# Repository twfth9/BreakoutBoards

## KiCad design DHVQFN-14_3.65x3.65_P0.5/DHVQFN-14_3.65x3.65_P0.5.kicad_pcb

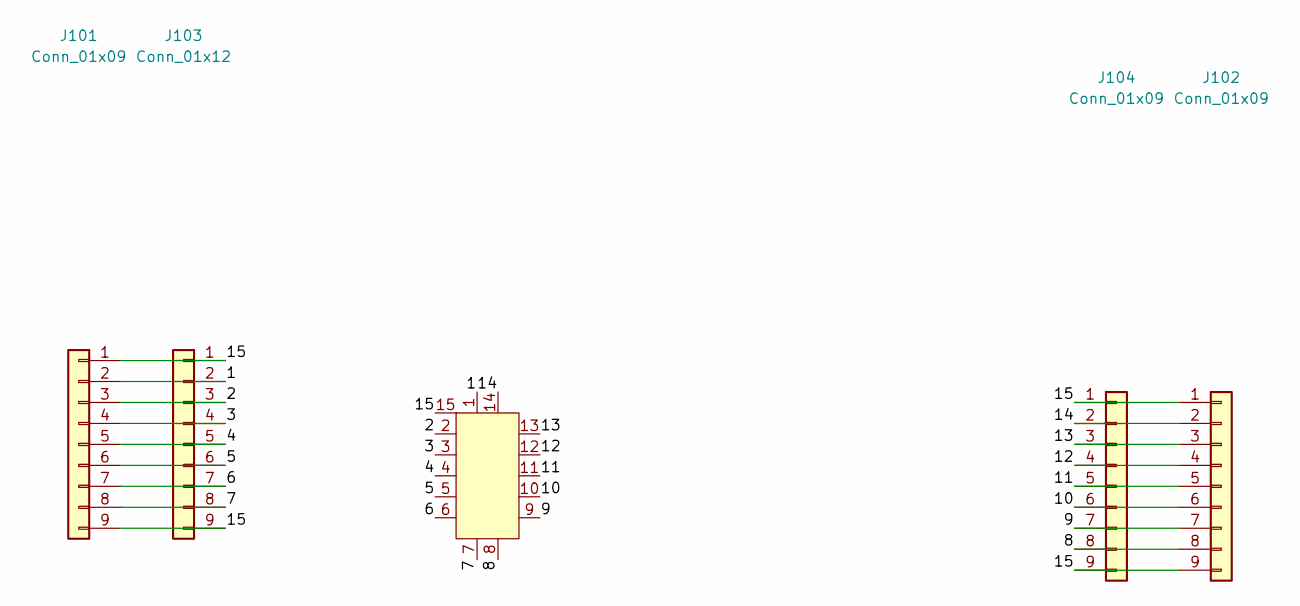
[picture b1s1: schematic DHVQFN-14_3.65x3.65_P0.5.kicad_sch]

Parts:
J101: Conn_01x09; PinHeader_1x09_P2.54mm_Vertical_SMD_Pin1Left
J102: Conn_01x09; PinHeader_1x09_P2.54mm_Vertical
J103: Conn_01x12; PinHeader_1x09_P2.54mm_Vertical
J104: Conn_01x09; PinHeader_1x09_P2.54mm_Vertical_SMD_Pin1Right
U101: DHVQFN-14; RGY14_2P05X2P05

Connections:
/1: J101.2, J103.2, U101.1
/2: J101.3, J103.3, U101.2
/3: J101.4, J103.4, U101.3
/4: J101.5, J103.5, U101.4
/5: J101.6, J103.6, U101.5
/6: J101.7, J103.7, U101.6
/7: J101.8, J103.8, U101.7
/8: J102.8, J104.8, U101.8
/9: J102.7, J104.7, U101.9
/10: J102.6, J104.6, U101.10
/11: J102.5, J104.5, U101.11
/12: J102.4, J104.4, U101.12
/13: J102.3, J104.3, U101.13
/14: J102.2, J104.2, U101.14
/15: J101.1, J101.9, J102.1, J102.9, J103.1, J103.9, J104.1, J104.9, U101.15

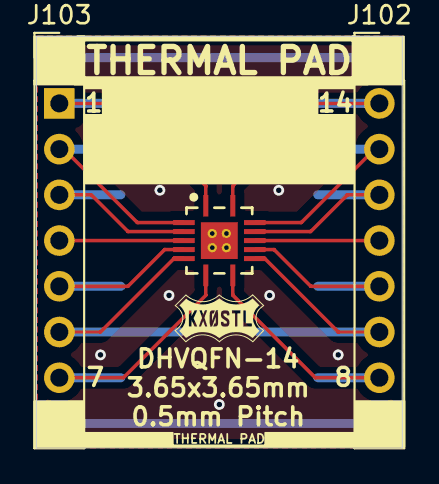
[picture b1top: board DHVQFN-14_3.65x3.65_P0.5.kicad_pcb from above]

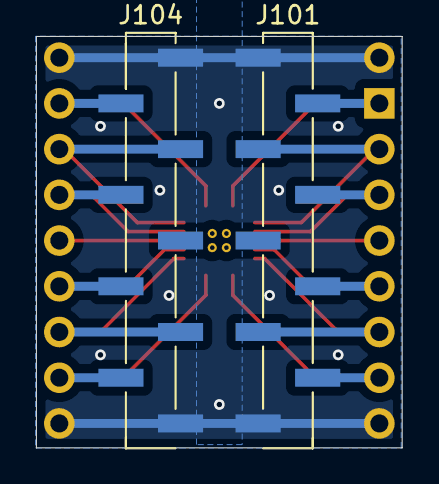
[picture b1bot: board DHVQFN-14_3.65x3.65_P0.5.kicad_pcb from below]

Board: 2 copper layers, 20.3 x 22.9 mm, 5 parts (2 on the bottom side), 15 nets.

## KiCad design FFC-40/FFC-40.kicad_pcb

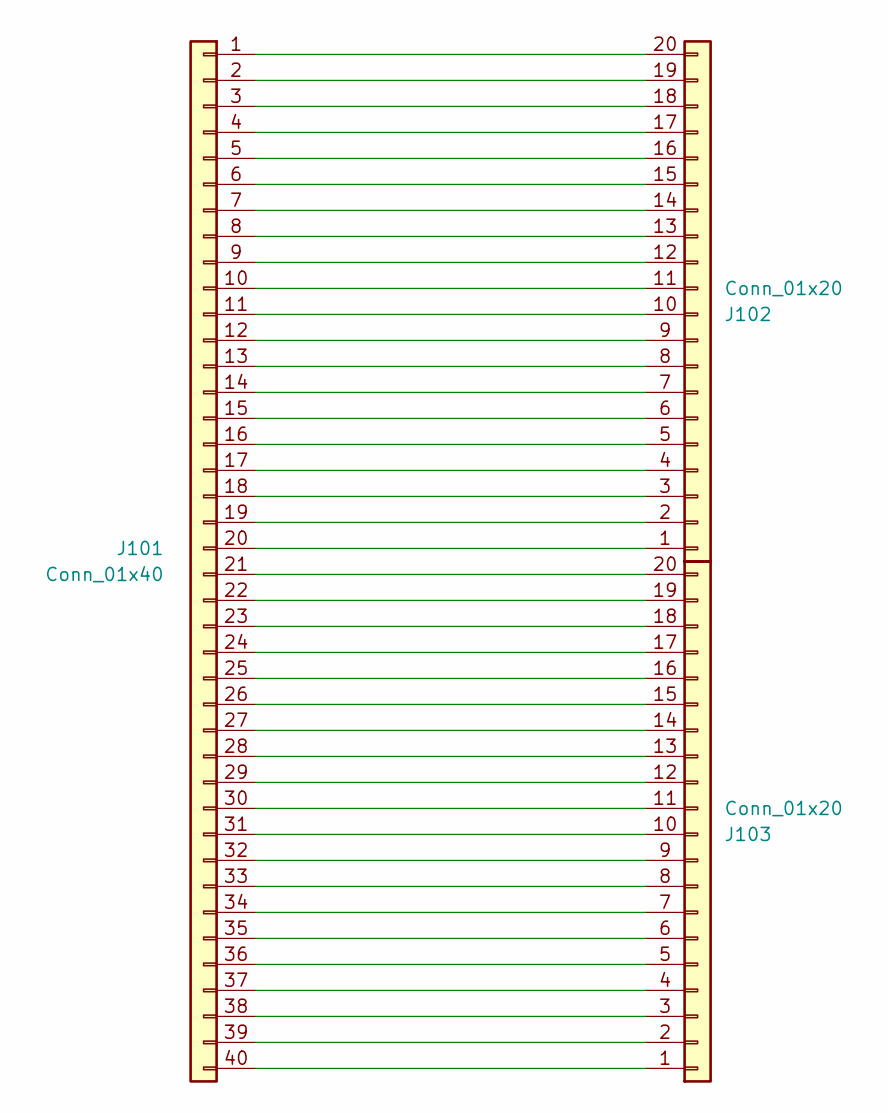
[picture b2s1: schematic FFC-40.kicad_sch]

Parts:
J101: Conn_01x40; Amphenol_F32R-1A7x1-11040_1x40-1MP_P0.5mm_Horizontal
J102, J103: Conn_01x20; PinHeader_1x20_P2.54mm_Vertical

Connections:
unnamed: J101.1, J102.20
unnamed: J101.2, J102.19
unnamed: J101.3, J102.18
unnamed: J101.4, J102.17
unnamed: J101.5, J102.16
unnamed: J101.6, J102.15
unnamed: J101.7, J102.14
unnamed: J101.8, J102.13
unnamed: J101.9, J102.12
unnamed: J101.10, J102.11
unnamed: J101.11, J102.10
unnamed: J101.12, J102.9
unnamed: J101.13, J102.8
unnamed: J101.14, J102.7
unnamed: J101.15, J102.6
unnamed: J101.16, J102.5
unnamed: J101.17, J102.4
unnamed: J101.18, J102.3
unnamed: J101.19, J102.2
unnamed: J101.20, J102.1
unnamed: J101.21, J103.20
unnamed: J101.22, J103.19
unnamed: J101.23, J103.18
unnamed: J101.24, J103.17
unnamed: J101.25, J103.16
unnamed: J101.26, J103.15
unnamed: J101.27, J103.14
unnamed: J101.28, J103.13
unnamed: J101.29, J103.12
unnamed: J101.30, J103.11
unnamed: J101.31, J103.10
unnamed: J101.32, J103.9
unnamed: J101.33, J103.8
unnamed: J101.34, J103.7
unnamed: J101.35, J103.6
unnamed: J101.36, J103.5
unnamed: J101.37, J103.4
unnamed: J101.38, J103.3
unnamed: J101.39, J103.2
unnamed: J101.40, J103.1

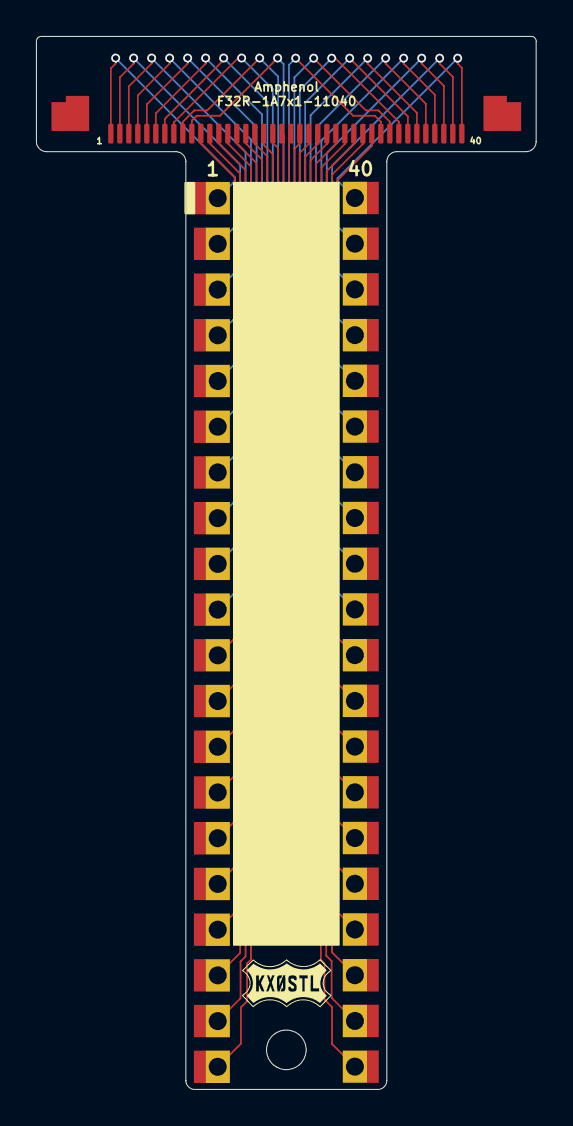
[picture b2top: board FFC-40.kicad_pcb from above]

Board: 2 copper layers, 27.8 x 58.5 mm, 3 parts (0 on the bottom side), 40 nets.

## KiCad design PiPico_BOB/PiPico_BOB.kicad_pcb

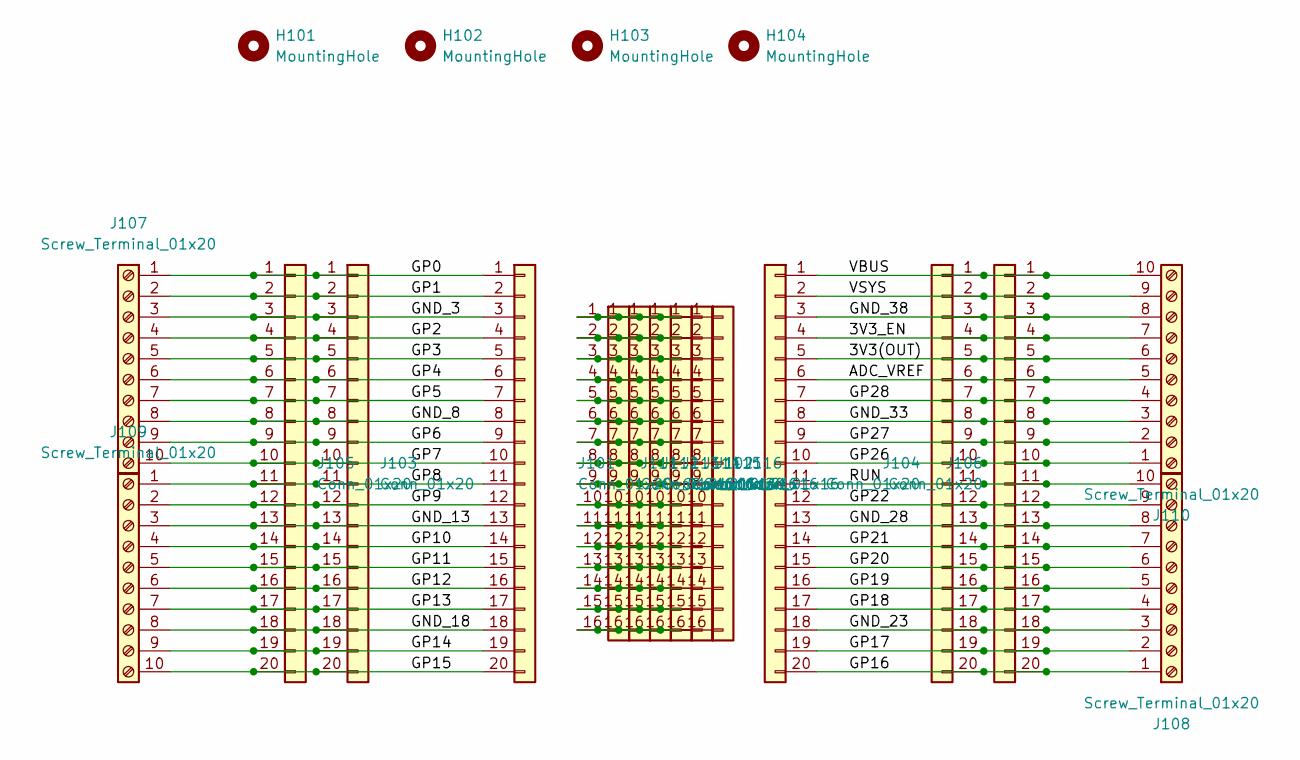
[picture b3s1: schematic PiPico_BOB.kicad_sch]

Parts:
H101, H102, H103, H104: MountingHole; MountingHole_2.2mm_M2
J101, J102, J103, J104: Conn_01x20; PinSocket_1x20_P2.54mm_Vertical
J105, J106: Conn_01x20; PinHeader_1x20_P2.54mm_Vertical
J107, J108, J109, J110: Screw_Terminal_01x20; TerminalBlock_Phoenix_MPT-0,5-10-2.54_1x10_P2.54mm_Horizont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
J111, J112, J113, J114, J115, J116: Conn_01x16; PinHeader_1x16_P2.54mm_Vertical

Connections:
/3V3(OUT): J102.5, J104.5, J106.5, J110.6
/3V3_EN: J102.4, J104.4, J106.4, J110.7
/ADC_VREF: J102.6, J104.6, J106.6, J110.5
/GND_3: J101.3, J103.3, J105.3, J107.3
/GND_8: J101.8, J103.8, J105.8, J107.8
/GND_13: J101.13, J103.13, J105.13, J109.3
/GND_18: J101.18, J103.18, J105.18, J109.8
/GND_23: J102.18, J104.18, J106.18, J108.3
/GND_28: J102.13, J104.13, J106.13, J108.8
/GND_33: J102.8, J104.8, J106.8, J110.3
/GND_38: J102.3, J104.3, J106.3, J110.8
/GP0: J101.1, J103.1, J105.1, J107.1
/GP1: J101.2, J103.2, J105.2, J107.2
/GP2: J101.4, J103.4, J105.4, J107.4
/GP3: J101.5, J103.5, J105.5, J107.5
/GP4: J101.6, J103.6, J105.6, J107.6
/GP5: J101.7, J103.7, J105.7, J107.7
/GP6: J101.9, J103.9, J105.9, J107.9
/GP7: J101.10, J103.10, J105.10, J107.10
/GP8: J101.11, J103.11, J105.11, J109.1
/GP9: J101.12, J103.12, J105.12, J109.2
/GP10: J101.14, J103.14, J105.14, J109.4
/GP11: J101.15, J103.15, J105.15, J109.5
/GP12: J101.16, J103.16, J105.16, J109.6
/GP13: J101.17, J103.17, J105.17, J109.7
/GP14: J101.19, J103.19, J105.19, J109.9
/GP15: J101.20, J103.20, J105.20, J109.10
/GP16: J102.20, J104.20, J106.20, J108.1
/GP17: J102.19, J104.19, J106.19, J108.2
/GP18: J102.17, J104.17, J106.17, J108.4
/GP19: J102.16, J104.16, J106.16, J108.5
/GP20: J102.15, J104.15, J106.15, J108.6
/GP21: J102.14, J104.14, J106.14, J108.7
/GP22: J102.12, J104.12, J106.12, J108.9
/GP26: J102.10, J104.10, J106.10, J110.1
/GP27: J102.9, J104.9, J106.9, J110.2
/GP28: J102.7, J104.7, J106.7, J110.4
/RUN: J102.11, J104.11, J106.11, J108.10
/VBUS: J102.1, J104.1, J106.1, J110.10
/VSYS: J102.2, J104.2, J106.2, J110.9
unnamed: J111.1, J112.1, J113.1, J114.1, J115.1, J116.1
unnamed: J111.2, J112.2, J113.2, J114.2, J115.2, J116.2
unnamed: J111.3, J112.3, J113.3, J114.3, J115.3, J116.3
unnamed: J111.4, J112.4, J113.4, J114.4, J115.4, J116.4
unnamed: J111.5, J112.5, J113.5, J114.5, J115.5, J116.5
unnamed: J111.6, J112.6, J113.6, J114.6, J115.6, J116.6
unnamed: J111.7, J112.7, J113.7, J114.7, J115.7, J116.7
unnamed: J111.8, J112.8, J113.8, J114.8, J115.8, J116.8
unnamed: J111.9, J112.9, J113.9, J114.9, J115.9, J116.9
unnamed: J111.10, J112.10, J113.10, J114.10, J115.10, J116.10
unnamed: J111.11, J112.11, J113.11, J114.11, J115.11, J116.11
unnamed: J111.12, J112.12, J113.12, J114.12, J115.12, J116.12
unnamed: J111.13, J112.13, J113.13, J114.13, J115.13, J116.13
unnamed: J111.14, J112.14, J113.14, J114.14, J115.14, J116.14
unnamed: J111.15, J112.15, J113.15, J114.15, J115.15, J116.15
unnamed: J111.16, J112.16, J113.16, J114.16, J115.16, J116.16

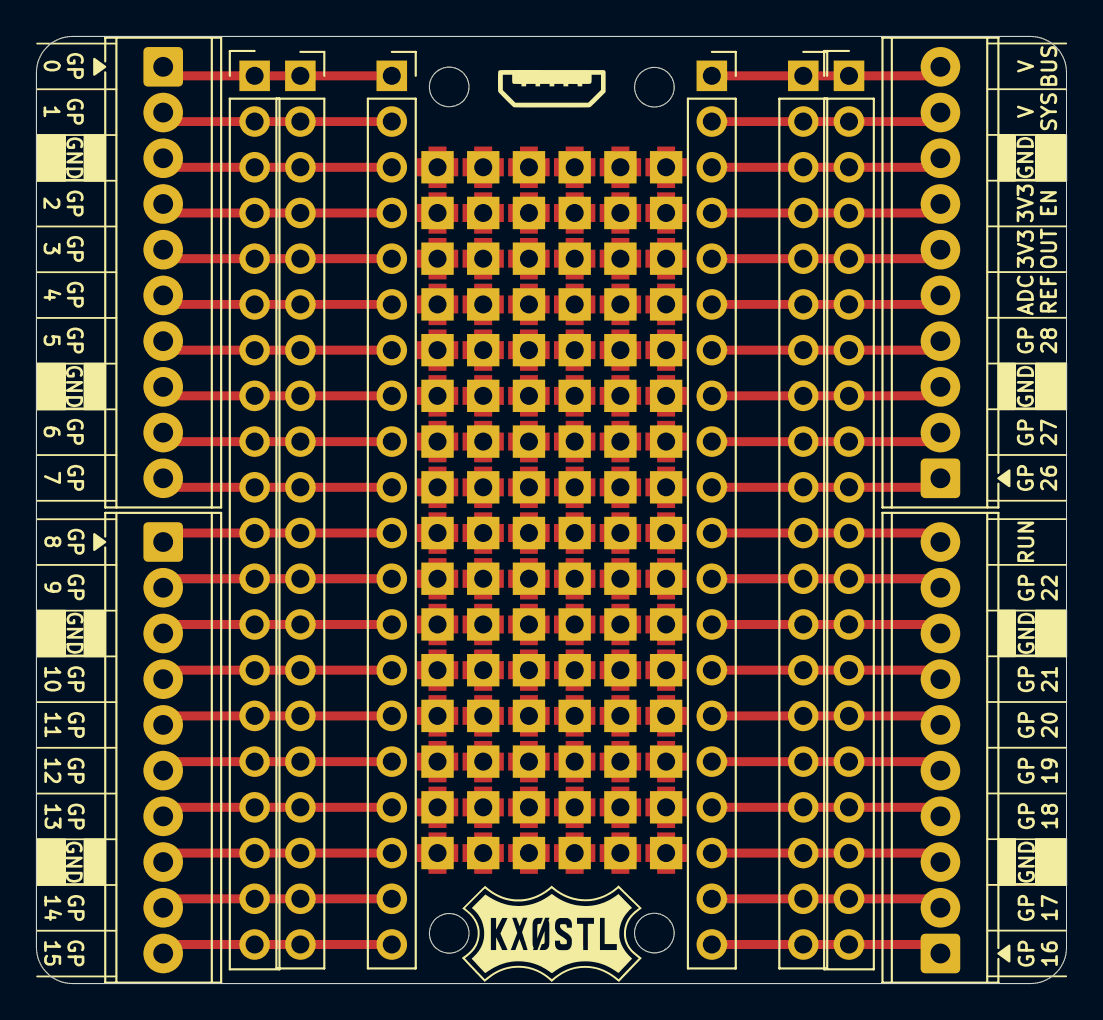
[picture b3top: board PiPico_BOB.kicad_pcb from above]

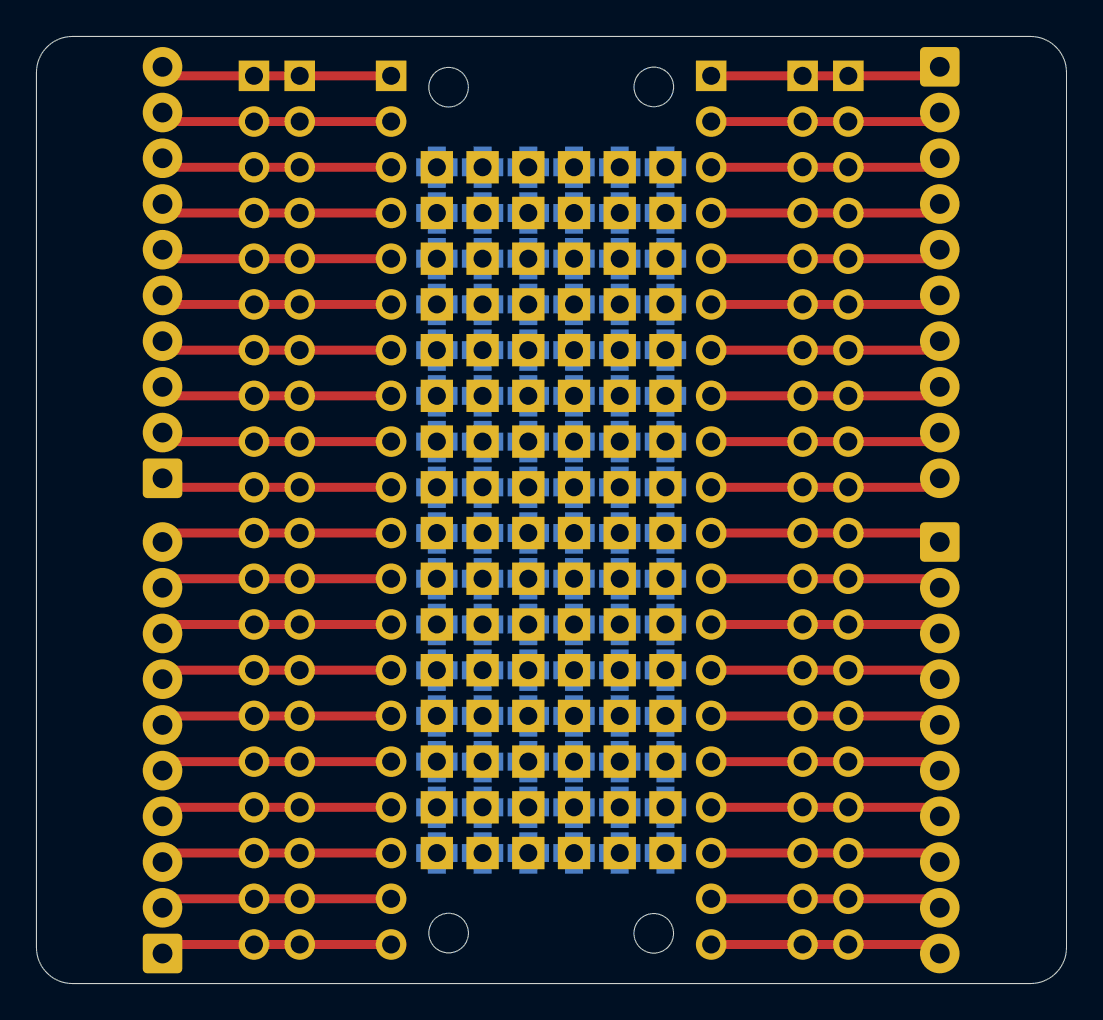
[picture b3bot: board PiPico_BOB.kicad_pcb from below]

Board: 2 copper layers, 57.2 x 52.6 mm, 20 parts (6 on the bottom side), 56 nets.
